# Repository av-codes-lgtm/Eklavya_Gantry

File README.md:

# **GantryMate-200: Automated Gantry-Based Screwing System**
|||
:-------------------------:|:-------------------------:|

## Table of Contents
1. [Problem Statement](#problem-statement)
2. [Our Solution](#our-solution)
   - [LED Panel Configuration](#led-panel-configuration)
   - [Critical Requirements](#critical-requirements)
3. [Features](#features)
4. [Prerequisites](#prerequisites)
5. [Repository Structure](#repository-structure)
6. [Installing](#installing)
7. [Hardware Architecture](#hardware-architecture)
8. [Future Goals](#future-goals)
9. [Authors](#authors)
10. [Acknowledgments](#acknowledgments)

---

## Problem Statement

**GantryMate-200** addresses the challenge of automating the precise handling of **~280 miniature screws (1 mm size)** on sensitive LED panels. The system must operate with extreme precision around delicate circuitry while maintaining high-speed performance.

## Our Solution

An advanced automated gantry system designed for precision screwing and unscrewing of miniature screws on delicate LED panels with sub-millimeter accuracy and high-speed operation.

[CAD MODEL](https://cad.onshape.com/documents/f8e877963d969bd52a009480/w/ae625ac84bd115da8b87aa91/e/6dbc831cc6b275fe37f96716) (Our CAD files)

### LED Panel Configuration

The target LED panel consists of two distinct layers:

* **Top Layer:** Contains **200 screws** - must be removed first during disassembly
* **Bottom Layer:** Contains **80 screws** - accessible only after top layer removal

**Installation Process:** Follows reverse order (bottom layer first, then top layer)

### Critical Requirements

Given the proximity to sensitive circuitry, the system must ensure:

- Sub-millimeter positioning repeatability
- Precise force control to prevent damage
- Accurate screw orientation detection
- Zero tolerance for misalignment
- Complete each screwing/unscrewing operation in **under 5 seconds**

## Features

- **High precision 3-axis gantry system** (X, Y, Z axes)
- **Specialized toolhead** with automated screw feeding mechanism
- **Sub-millimeter(0.05mm resolution) positioning accuracy**
- **High-speed operation** (<5 seconds per screw to be achieved)
- **Automated screw orientation** ensuring correct placement(to be achieved)

### Prerequisites

Hardware requirements:
- ESP32 development board
- DRV8825 stepper motor drivers (3x for X, Y, Z axes)
- Nema 17 Stepper motors (3x for gantry movement)
- Power supply (appropriate voltage/current for your stepper motors)
- Mechanical components (rails, belts, pulleys, frame, etc)

Software used:
- [ESP-IDF](https://docs.espressif.com/projects/esp-idf/en/latest/esp32/get-started/) (development framework) 
- [KiCad](https://www.kicad.org/) (for PCB modifications)
- [Onshape](https://www.onshape.com/) (for Mechanical Design)
- Git for version control.

### Repository Structure

```
Eklavya_Gantry
├── Docs/
├── Firmware/
│   ├── DRV8825/                   #Code for Running the system on DRV8825   
│   │   ├── circle/
│   │   ├── Double_axes/
│   │   ├── final/
│   │   ├── go_to_pos/
│   │   ├── homing/
│   │   ├── limit/
│   │   ├── SRA/
│   │   ├── step_func/
│   │   ├── stepper_test/
│   │   ├── totalhoming/
│   │   └── total_positioning/
│   ├── TMC2208/                   #Code for Running the system on TMC2208
│   │   ├── Go_to_pos/
│   │   ├── step_func/
│   │   └── uart/
│   │       ├── nmea0183_parser/
│   │       ├── uart_async_rxtxtasks/
│   │       ├── uart_echo/
│   │       ├── uart_echo_rs485/
│   │       ├── uart_events/
│   │       ├── uart_repl/
│   │       └── uart_select/
│   └── Screwdriver/               #Code for operating the toolhead
│       └── Screw/
├── Mechanics/
│   .
│   .
│   └── STL files for 3D Printed parts
├── PCB/
|   .
|   .
|   └── KiCad Files for PCB
└── README.md

```

### Installing

Step-by-step setup process:

1. **Clone the repository**
```bash
git clone https://github.com/av-codes-lgtm/Eklavya_Gantry.git
cd Eklavya_Gantry
```

2. **Build and flash firmware**

Go to the folder with the code you want to flash to the esp using 

```bash
cd /Eklavya_Gantry/Firmware/folder-of-your-choice
```

and then run the following code

```bash
idf.py build flash monitor
```

## Hardware Architecture

| Component | Description |
|-----------|-------------|
| [ESP32](https://www.espressif.com/en/products/socs/esp32) | Main microcontroller with WiFi/Bluetooth capability |
| [DRV8825 Stepper Drivers](https://www.pololu.com/product/2133) | High-performance microstepping motor drivers |
| Nema 17 Stepper Motors | Precision motors for X, Y, Z axis control |
| Custom PCB | Integrated control and driver circuitry (under development) |

## Future Goals
- Shift to TMC2208 stepper drivers for better current handling and power distribution. DRV8825 does not work for prolonged time periods.
- Finalising the circuitry and shifting completely to PCB.
- Fine tuning the screw in and screw out processes to achieve industry grade quality screwing.
- Add a screw feeding system for the "screwing in" process.
- Creating a feedback mechanism to verify Screwing and unscrewing
- Creating a UI (Either WebPortal or build in software controlled using Raspberry Pi and a small screen) to make operation of the system simpler.
## Authors
*  *Firmware and Hardware setup*- [Aryan_Vyapari](https://github.com/av-codes-lgtm)
*  *PCB Design and tool-head operation* - [Sarvaarth_Narang](https://github.com/SarvaarthN)
*  *Firmware and Hardware setup* - [Pushkar_Dube](https://github.com/pushkardube)  

See the list of [contributors](https://github.com/av-codes-lgtm/Eklavya_Gantry/graphs/contributors) who participated in this project.
## Acknowledgments

* Thanks to the ESP-IDF, KiCad and Onshape community for excellent development tools
* Inspiration from industrial automation and precision manufacturing
- Thanks to our Robotics Club [SRA-VJTI](https://github.com/sra-vjti)  
* Special thanks to our senior mentors [Amey_Tikhe](https://github.com/AmeyaTikhe)  &  [Varun_Nigudkar](https://github.com/fluffysunfish?tab=overview&from=2024-12-01&to=2024-12-31)  

---

**For technical support, feature requests, or bug reports, please open an issue on GitHub.**

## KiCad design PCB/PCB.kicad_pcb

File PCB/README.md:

# DRV8825 Stepper Motor Driver with ESP32 and Limit Switch

This project demonstrates how to control a stepper motor using an **ESP32**, a **DRV8825 motor driver**, and a **limit switch** for homing or safety purposes. 

---

## Circuit Description

The **ESP32** sends step and direction signals to the **DRV8825**, which drives a bipolar stepper motor.  
A **limit switch** is added to detect the end position or provide a safe stop.

---

## Connections

### DRV8825 → Stepper Motor
- **A1, A2, B1, B2** → Connect to stepper motor coils  
  - A coil: A1, A2  
  - B coil: B1, B2  

### DRV8825 → ESP32
- **STEP** → GPIO 18 (pulse to step motor)  
- **DIR** → GPIO 19 (sets rotation direction)  
- **EN (Enable)** → GPIO 21 (active LOW, optional)  
- **GND** → ESP32 GND  
- **VMOT** → External motor supply (8.2–45V depending on motor) but for this Project 12V was used
- **GND (Motor)** → Power supply ground  

**Important:** Place a 100µF electrolytic capacitor across VMOT and GND close to the DRV8825 to protect against voltage spikes.  

### Limit Switch → ESP32
- One terminal → GPIO 23  
- Other terminal → GND  
- Use **internal pull-up resistor** in ESP32 code.  

---

## Circuit Diagram

```plaintext
              +-------------------+
   VMOT 8-45V |                   | Stepper Motor
   + ---------| VMOT        A1 ---|---- Coil A
   - ---------| GND         A2 ---|---- Coil A
              |                   |
ESP32 GPIO 18 | STEP        B1 ---|---- Coil B
ESP32 GPIO 19 | DIR         B2 ---|---- Coil B
ESP32 GPIO 21 | EN                |
ESP32   GND - | GND               |
              +-------------------+

Limit Switch:
  GPIO 23 ---/ ---- GND

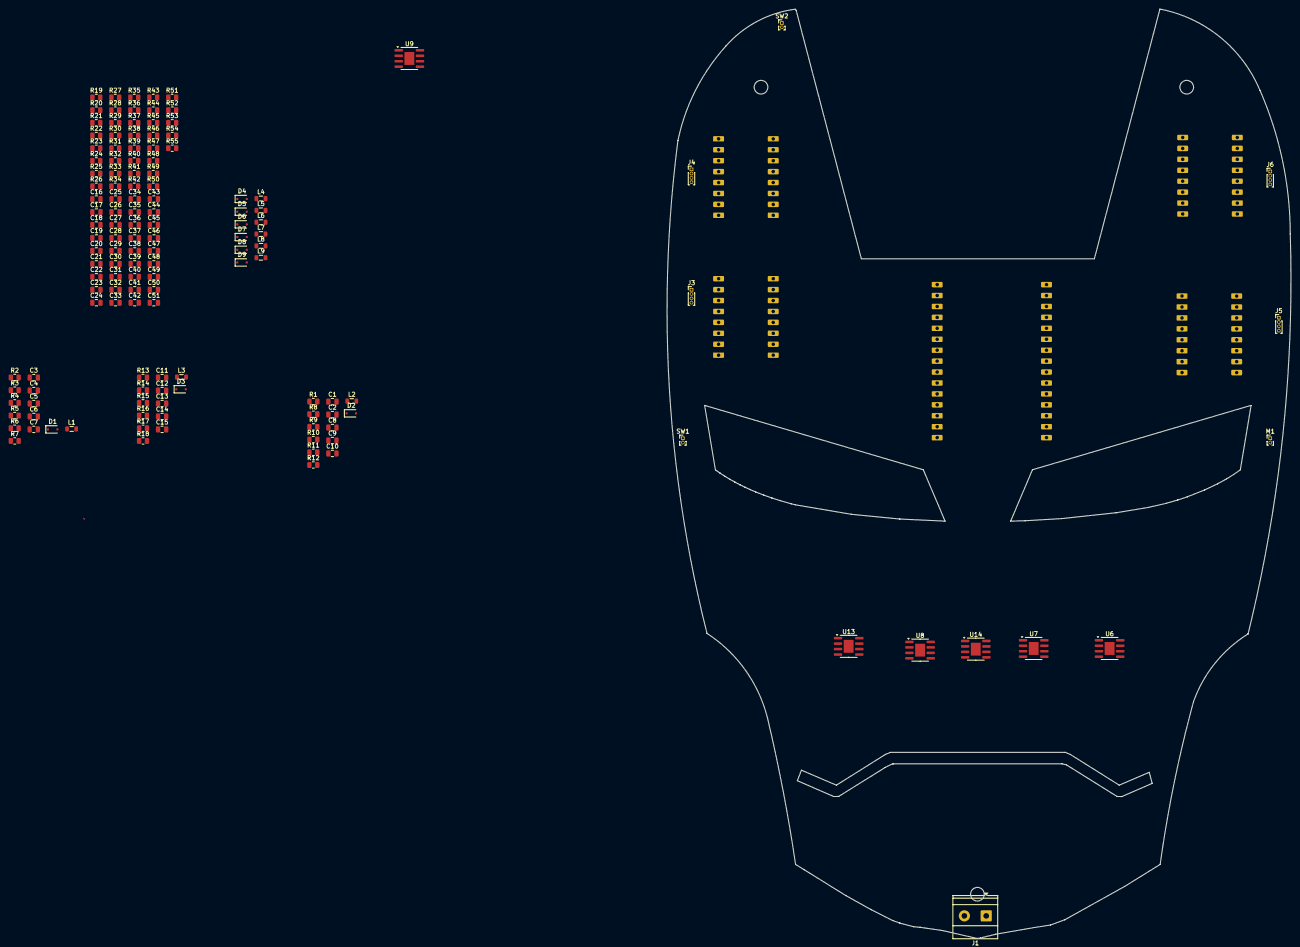
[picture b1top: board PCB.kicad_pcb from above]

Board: 2 copper layers, 145.0 x 216.0 mm, 143 parts (0 on the bottom side), 82 nets.

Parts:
C1, C7, C11, C16, C21, C26, C31, C39, C46: 10 uF; C_0805_2012Metric
C2, C3, C12, C17, C22, C27, C32, C40, C47: 100 nF; C_0805_2012Metric
C4, C10, C15, C20, C25, C30, C35, C43, C50: 22 uF; C_0805_2012Metric
C5, C8, C13, C18, C23, C28, C33, C41, C48: 220 pF; C_0805_2012Metric
C6, C9, C14, C19, C24, C29, C34, C42, C49: NS; C_0805_2012Metric
C36, C37, C38, C44, C51: 100 uF; C_0805_2012Metric
C45: 0.1 uF; C_0805_2012Metric
D1, D2, D3, D4, D5, D6, D7, D8, D9: D_Zener_Small; D_SOD-323F
J1: Screw_Terminal_01x02; TerminalBlock_Phoenix_MKDS-1,5-2-5.08_1x02_P5.08mm_Horizont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
J2: esp32 30 pin; ESP32 30 pin
J3, J4, J5, J6: JST; PinHeader_1x04_P1.00mm_Vertical
L1, L2, L3, L4, L5, L6, L7, L8, L9: L_Small; L_0805_2012Metric
M1: Motor_DC; PinHeader_1x02_P1.00mm_Vertical
R1, R7, R13, R19, R25, R31, R37, R43, R50: 24.9k; R_0805_2012Metric
R2, R18, R24, R30, R36, R48, R55: 140k; R_0805_2012Metric
R3, R17, R23, R29, R35, R47, R54: 10k; R_0805_2012Metric
R4, R10, R16, R22, R28, R34, R40, R46, R53: 68.1k; R_0805_2012Metric
R5, R8, R14, R20, R26, R32, R38, R44, R51: 200k; R_0805_2012Metric
R6, R9, R15, R21, R27, R33, R39, R45, R52: 100k; R_0805_2012Metric
R11, R41: 4.3k; R_0805_2012Metric
R12, R42: 22k; R_0805_2012Metric
R49: 0.1 k; R_0805_2012Metric
SW1, SW2: SW_SPDT_XKB_DMx-xxxx-1; PinHeader_1x02_P1.00mm_Vertical
U6, U7, U8, U9, U13, U14: SOIC-8-1EP_3.9x4.9mm_P1.27mm_EP2.29x3mm
U10, U11, U12, U15: DRV8825_STEPPER_MOTOR_DRIVER_CARRIER; DRV8825Module

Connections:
/Assembly/3v3: J2.16 (3V3), SW1.1 (A), SW2.1 (A), U10.2 (M0), U10.3 (M1), U10.4 (M2), U10.5 (~RST), U10.6 (~SLP), U11.2 (M0), U11.3 (M1), U11.4 (M2), U11.5 (~RST), U11.6 (~SLP), U12.2 (M0), U12.3 (M1), U12.4 (M2), U12.5 (~RST), U12.6 (~SLP), U15.2 (M0), U15.3 (M1), U15.4 (M2), U15.5 (~RST), U15.6 (~SLP)
/Assembly/28V: C16.2, C21.2, C26.2, C31.2, C39.2, C46.2, J1.2, R21.1, R27.1, R33.1, R39.1, R45.1, R52.1, U6.7 (VIN), U7.7 (VIN), U8.7 (VIN), U9.7 (VIN), U13.7 (VIN), U14.7 (VIN)
/Assembly/D2: J2.19 (D2), U10.7 (STEP), U15.8 (DIR)
/Assembly/D4: J2.20 (D4), U10.8 (DIR), U15.7 (STEP)
/Assembly/D18: J2.24 (D18), U11.7 (STEP)
/Assembly/D19: J2.25 (D19), U11.8 (DIR)
/Assembly/GND_L: J2.17 (GND), U10.9 (GND), U11.9 (GND), U12.9 (GND), U15.9 (GND)
Earth: C1.1, C4.1, C6.2, C7.1, C9.2, C10.1, C11.1, C14.2, C15.1, C16.1, C19.2, C20.1, C21.1, C24.2, C25.1, C26.1, C29.2, C30.1, C31.1, C34.2, C35.1, C39.1, C42.2, C43.1, C46.1, C49.2, C50.1, D1.2 (A), D2.2 (A), D3.2 (A), D4.2 (A), D5.2 (A), D6.2 (A), D7.2 (A), D8.2 (A), D9.2 (A), J1.1, M1.2 (-), R1.2, R3.2, R4.2, R5.2, R7.2, R8.2, R10.2, R11.2, R13.2, R14.2, R16.2, R17.2, R19.2, R20.2, R22.2, R23.2, R25.2, R26.2, R28.2, R29.2, R31.2, R32.2, R34.2, R35.2, R37.2, R38.2, R40.2, R41.2, R43.2, R44.2, R46.2, R47.2, R49.2, R50.2, R51.2, R53.2, R54.2, U6.5 (GND), U7.5 (GND), U8.5 (GND), U9.5 (GND), U10.15 (GND_MOT), U11.15 (GND_MOT), U12.15 (GND_MOT), U13.5 (GND), U14.5 (GND), U15.15 (GND_MOT)
unnamed: C4.2, L1.2, R2.2
unnamed: C5.2, R4.1
unnamed: C8.2, R10.1
unnamed: C10.2, L2.2, R12.2
unnamed: C13.2, R16.1
unnamed: C15.2, L3.2, R18.2
unnamed: C18.2, R22.1
unnamed: C23.2, R28.1
unnamed: C28.2, R34.1
unnamed: C33.2, R40.1
unnamed: C41.2, R46.1
unnamed: C45.2, R49.1
unnamed: C48.2, R53.1
unnamed: C3.2, D1.1 (K), L1.1
unnamed: C2.2, D2.1 (K), L2.1
unnamed: C12.2, D3.1 (K), L3.1
unnamed: C17.2, D4.1 (K), L4.1, U6.1 (SW)
unnamed: C22.2, D5.1 (K), L5.1, U7.1 (SW)
unnamed: C27.2, D6.1 (K), L6.1, U8.1 (SW)
unnamed: C32.2, D7.1 (K), L7.1, U9.1 (SW)
unnamed: C40.2, D8.1 (K), L8.1, U13.1 (SW)
unnamed: C47.2, D9.1 (K), L9.1, U14.1 (SW)
unnamed: C35.2, L7.2, R42.2
unnamed: J3.1, U10.12 (A1)
unnamed: J3.2, U10.11 (A2)
unnamed: J3.3, U10.13 (B1)
unnamed: J3.4, U10.14 (B2)
unnamed: J4.1, U11.12 (A1)
unnamed: J4.2, U11.11 (A2)
unnamed: J4.3, U11.13 (B1)
unnamed: J4.4, U11.14 (B2)
unnamed: J5.1, U12.12 (A1)
unnamed: J5.2, U12.11 (A2)
unnamed: J5.3, U12.13 (B1)
unnamed: J5.4, U12.14 (B2)
unnamed: J6.1, U15.12 (A1)
unnamed: J6.2, U15.11 (A2)
unnamed: J6.3, U15.13 (B1)
unnamed: J6.4, U15.14 (B2)
unnamed: C43.2, C44.1, C44.2, C45.1, L8.2, M1.1 (+), R48.2
unnamed: C8.1, C9.1
unnamed: R1.1, R9.2
unnamed: R11.1, R12.1
unnamed: C1.2, R9.1
unnamed: C5.1, C6.1
unnamed: R6.2, R7.1
unnamed: R2.1, R3.1
unnamed: C7.2, R6.1
unnamed: C13.1, C14.1
unnamed: R13.1, R15.2
unnamed: R17.1, R18.1
unnamed: C11.2, R15.1
unnamed: C18.1, C19.1, U6.3 (COMP)
unnamed: R19.1, R21.2, U6.2 (EN)
unnamed: R23.1, R24.1, U6.4 (FB)
unnamed: C23.1, C24.1, U7.3 (COMP)
unnamed: R25.1, R27.2, U7.2 (EN)
unnamed: R29.1, R30.1, U7.4 (FB)
unnamed: C28.1, C29.1, U8.3 (COMP)
unnamed: R31.1, R33.2, U8.2 (EN)
unnamed: R35.1, R36.1, U8.4 (FB)
unnamed: R37.1, R39.2, U9.2 (EN)
unnamed: C33.1, C34.1, U9.3 (COMP)
unnamed: R41.1, R42.1, U9.4 (FB)
unnamed: C20.2, C36.1, C36.2, L4.2, R24.2, U10.16 (VMOT)
unnamed: C25.2, C37.1, C37.2, L5.2, R30.2, U11.16 (VMOT)
unnamed: C30.2, C38.1, C38.2, L6.2, R36.2, U12.16 (VMOT)
unnamed: C41.1, C42.1, U13.3 (COMP)
unnamed: R43.1, R45.2, U13.2 (EN)
unnamed: R47.1, R48.1, U13.4 (FB)
unnamed: C48.1, C49.1, U14.3 (COMP)
unnamed: R50.1, R52.2, U14.2 (EN)
unnamed: R54.1, R55.1, U14.4 (FB)
unnamed: C50.2, C51.1, C51.2, L9.2, R55.2, U15.16 (VMOT)

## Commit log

2025-07-26 EVERYTHING
2025-07-26 step_func
2025-07-27 Emptying the repo
2025-07-28 homing and other projects
2025-07-28 Remove build files and add to .gitignore
2025-07-30 positioning with homing
2025-07-30 some edits
2025-08-01 fixing the step_func folder issue
2025-08-02 Fixed the bug in positioning code
2025-08-04 Added Schematic for MP 1584 5V and 12V
2025-08-04 Created README.md
2025-08-04 Added Structure
2025-08-04 Added Structure more
2025-08-06 schematic n footprints of drv n esp32
2025-08-06 Added Schematic
2025-08-11 Some Stl files
2025-08-15 some minor updates
2025-08-15 Updated Schematic with labels
2025-08-15 Double axes attempts
2025-08-15 fixed the homing error
2025-08-15 freeRTOS implementation
2025-08-17 commits after radius tuning
2025-08-17 Limit switch test
2025-08-20 2d positioning code
2025-08-21 Added Some Footprints
2025-08-21 Added simultaneously straight line positioning
2025-08-26 Tracing SRA
2025-08-31 fixed homing in total positioning
2025-08-31 Seperated folders for TMC2208 and DRV8825
2025-08-31 added sample code for TMC2208, awaiting testing
2025-09-03 Added some more code
2025-09-04 Added basic Screwdriver Code
2025-09-05 Updating README
2025-09-06 Fully functional 3-axis code for gantry
2025-09-06 Added Stepper Motor Driver Docs
2025-09-06 Create LICENSE
2025-09-06 Screenshots of CAD model
2025-09-06 Added PCB files and readme
2025-09-06 Added README
